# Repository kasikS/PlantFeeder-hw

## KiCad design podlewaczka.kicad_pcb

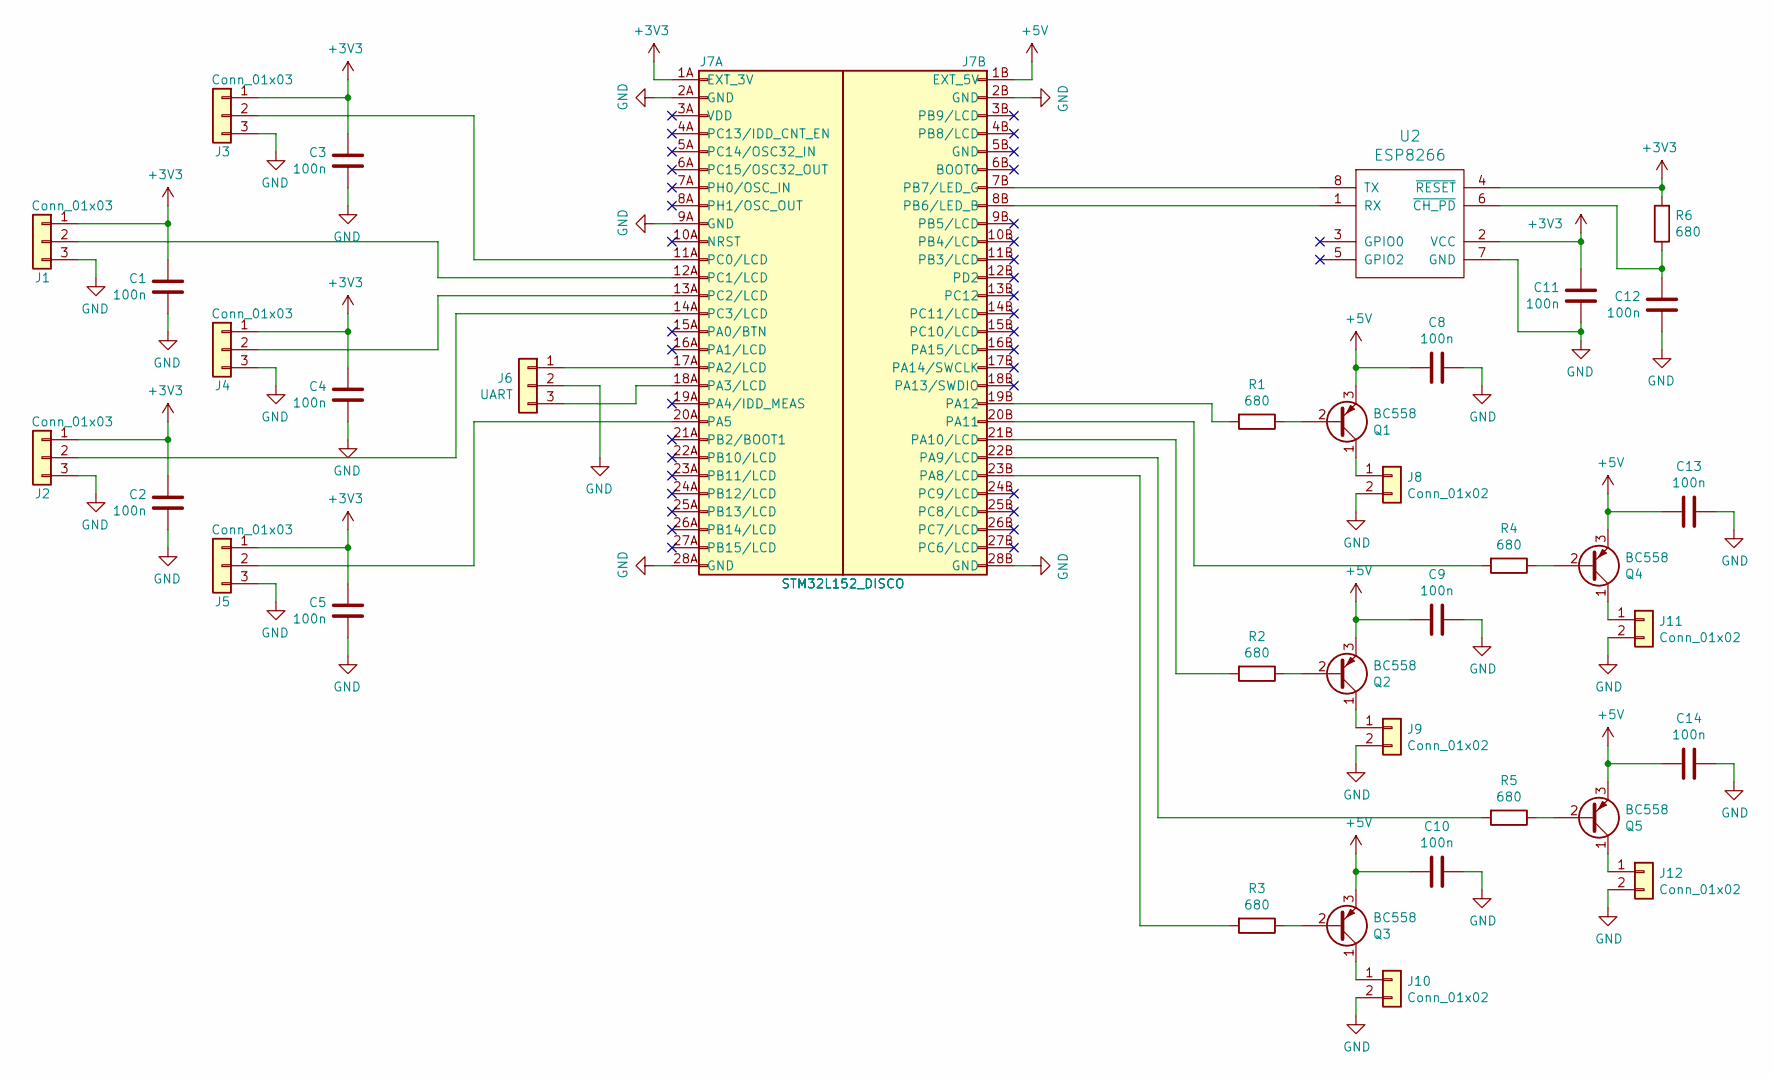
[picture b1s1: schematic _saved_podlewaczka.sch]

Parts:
C1, C2, C3, C4, C5, C8, C9, C10, C11, C12, C13, C14: 100n; CAPR500-250X720X650
J1, J2, J3, J4, J5: Conn_01x03; PhoenixContact_MC-G_03x3.50mm_Angled
J6: UART; Pin_Header_Straight_1x03_Pitch2.54mm
J7: STM32L152_DISCO
J8, J9, J10, J11, J12: Conn_01x02; PhoenixContact_MC-G_02x3.50mm_Angled
Q1, Q2, Q3, Q4, Q5: BC558; TO-92_Molded_Narrow
R1, R2, R3, R4, R5, R6: 680; RES1016-630X250
U2: ESP8266; Pin_Header_Angled_2x04_Pitch2.54mm

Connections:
+3V3: C1.2, C2.2, C3.2, C4.2, C5.2, C11.2, J1.1, J2.1, J3.1, J4.1, J5.1, J7.1A (EXT_3V), R6.2, U2.2 (VCC), U2.4 (~RESET)
+5V: C8.2, C9.2, C10.2, C13.2, C14.2, J7.1B (EXT_5V), Q1.3 (E), Q2.3 (E), Q3.3 (E), Q4.3 (E), Q5.3 (E)
GND: C1.1, C2.1, C3.1, C4.1, C5.1, C8.1, C9.1, C10.1, C11.1, C12.1, C13.1, C14.1, J1.3, J2.3, J3.3, J4.3, J5.3, J6.2, J7.2A (GND), J7.2B (GND), J7.9A (GND), J7.28A (GND), J7.28B (GND), J8.2, J9.2, J10.2, J11.2, J12.2, U2.7 (GND)
unnamed: C12.2, R6.1, U2.6 (~CH_PD)
unnamed: J1.2, J7.12A (PC1/LCD)
unnamed: J2.2, J7.14A (PC3/LCD)
unnamed: J3.2, J7.11A (PC0/LCD)
unnamed: J4.2, J7.13A (PC2/LCD)
unnamed: J5.2, J7.20A (PA5)
unnamed: J6.1, J7.17A (PA2/LCD)
unnamed: J6.3, J7.18A (PA3/LCD)
unnamed: J7.7B (PB7/LED_G), U2.8 (TX)
unnamed: J7.8B (PB6/LED_B), U2.1 (RX)
unnamed: J7.19B (PA12), R1.2
unnamed: J7.20B (PA11), R4.2
unnamed: J7.21B (PA10/LCD), R2.2
unnamed: J7.22B (PA9/LCD), R5.2
unnamed: J7.23B (PA8/LCD), R3.2
unnamed: J8.1, Q1.1 (C)
unnamed: J9.1, Q2.1 (C)
unnamed: J10.1, Q3.1 (C)
unnamed: J11.1, Q4.1 (C)
unnamed: J12.1, Q5.1 (C)
unnamed: Q1.2 (B), R1.1
unnamed: Q2.2 (B), R2.1
unnamed: Q3.2 (B), R3.1
unnamed: Q4.2 (B), R4.1
unnamed: Q5.2 (B), R5.1

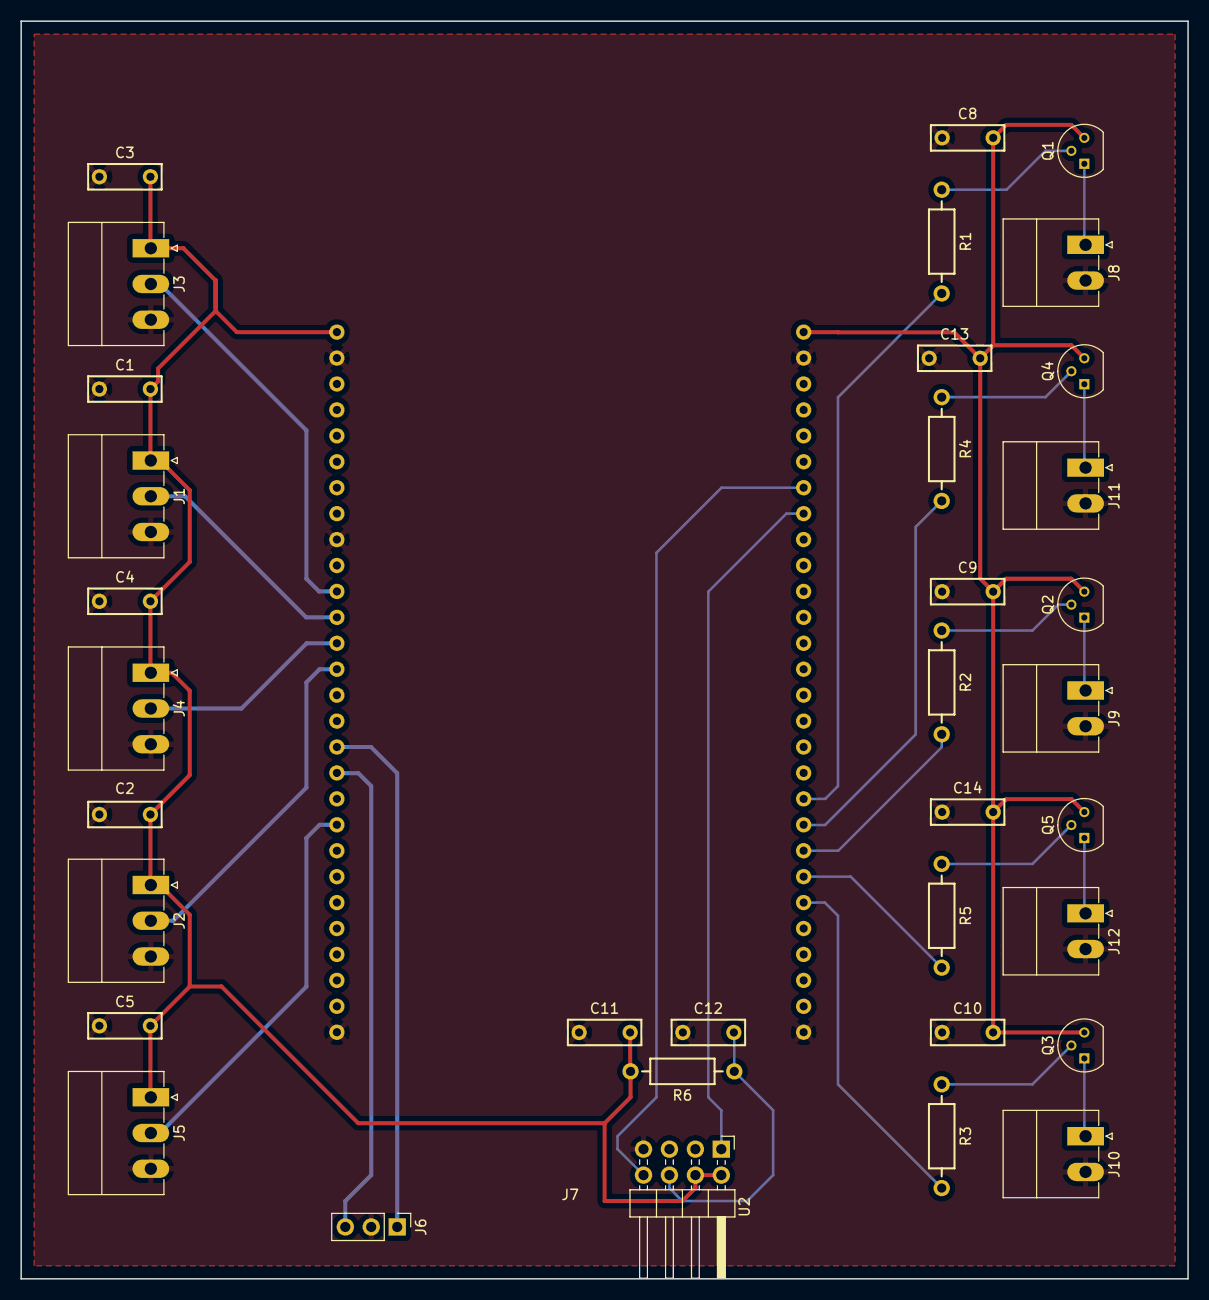
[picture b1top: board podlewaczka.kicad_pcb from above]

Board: 2 copper layers, 114.3 x 123.2 mm, 36 parts (0 on the bottom side), 28 nets.
